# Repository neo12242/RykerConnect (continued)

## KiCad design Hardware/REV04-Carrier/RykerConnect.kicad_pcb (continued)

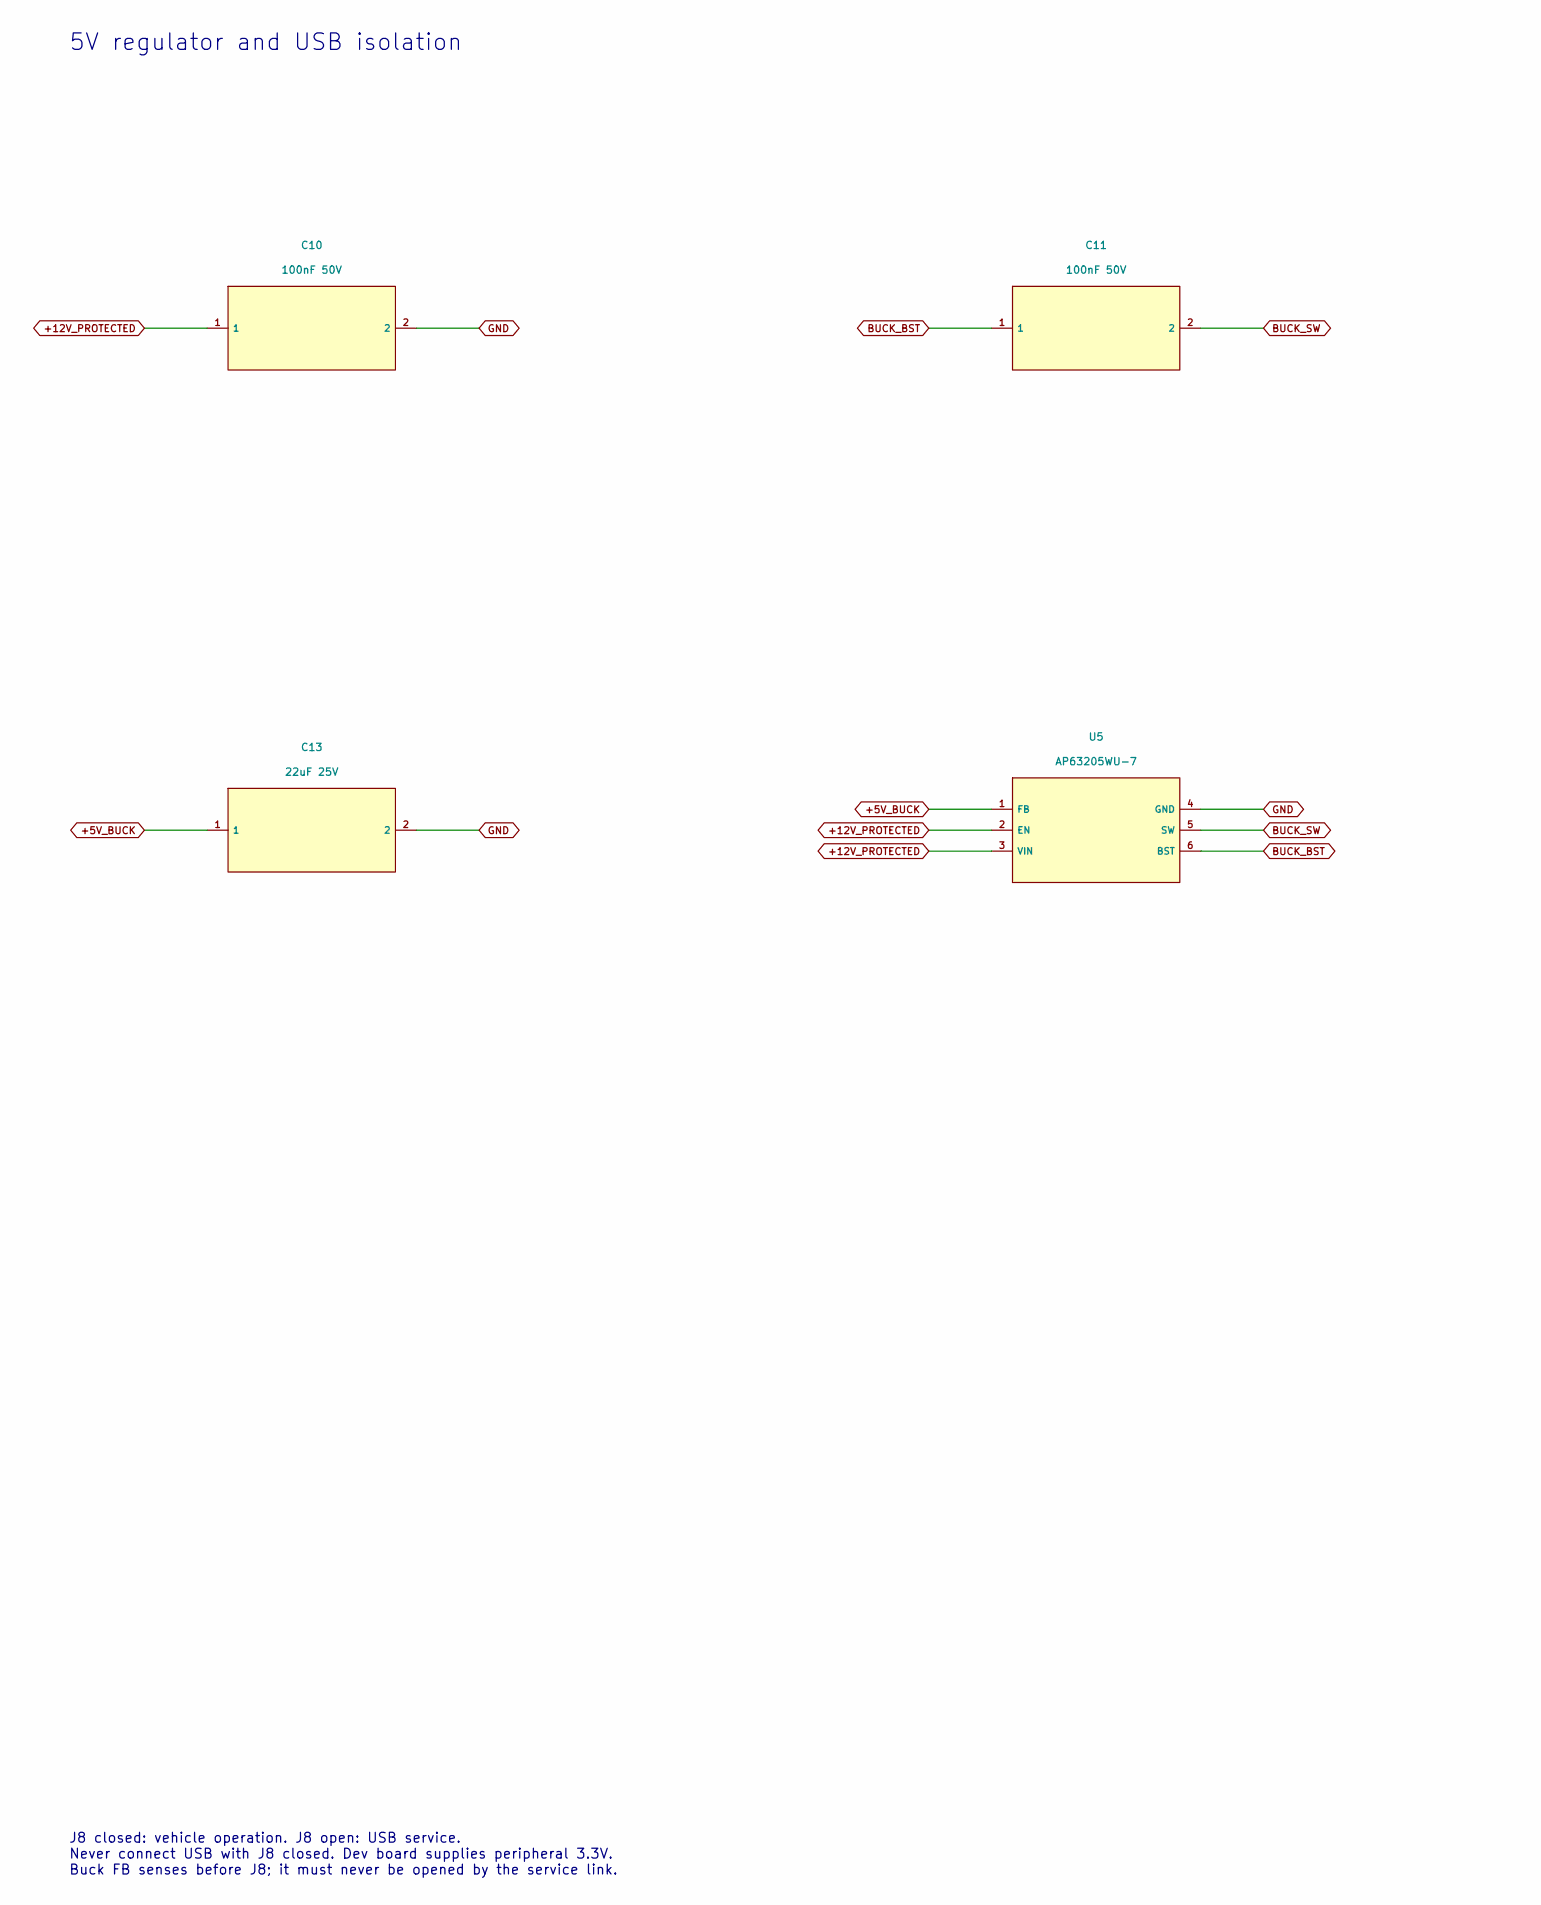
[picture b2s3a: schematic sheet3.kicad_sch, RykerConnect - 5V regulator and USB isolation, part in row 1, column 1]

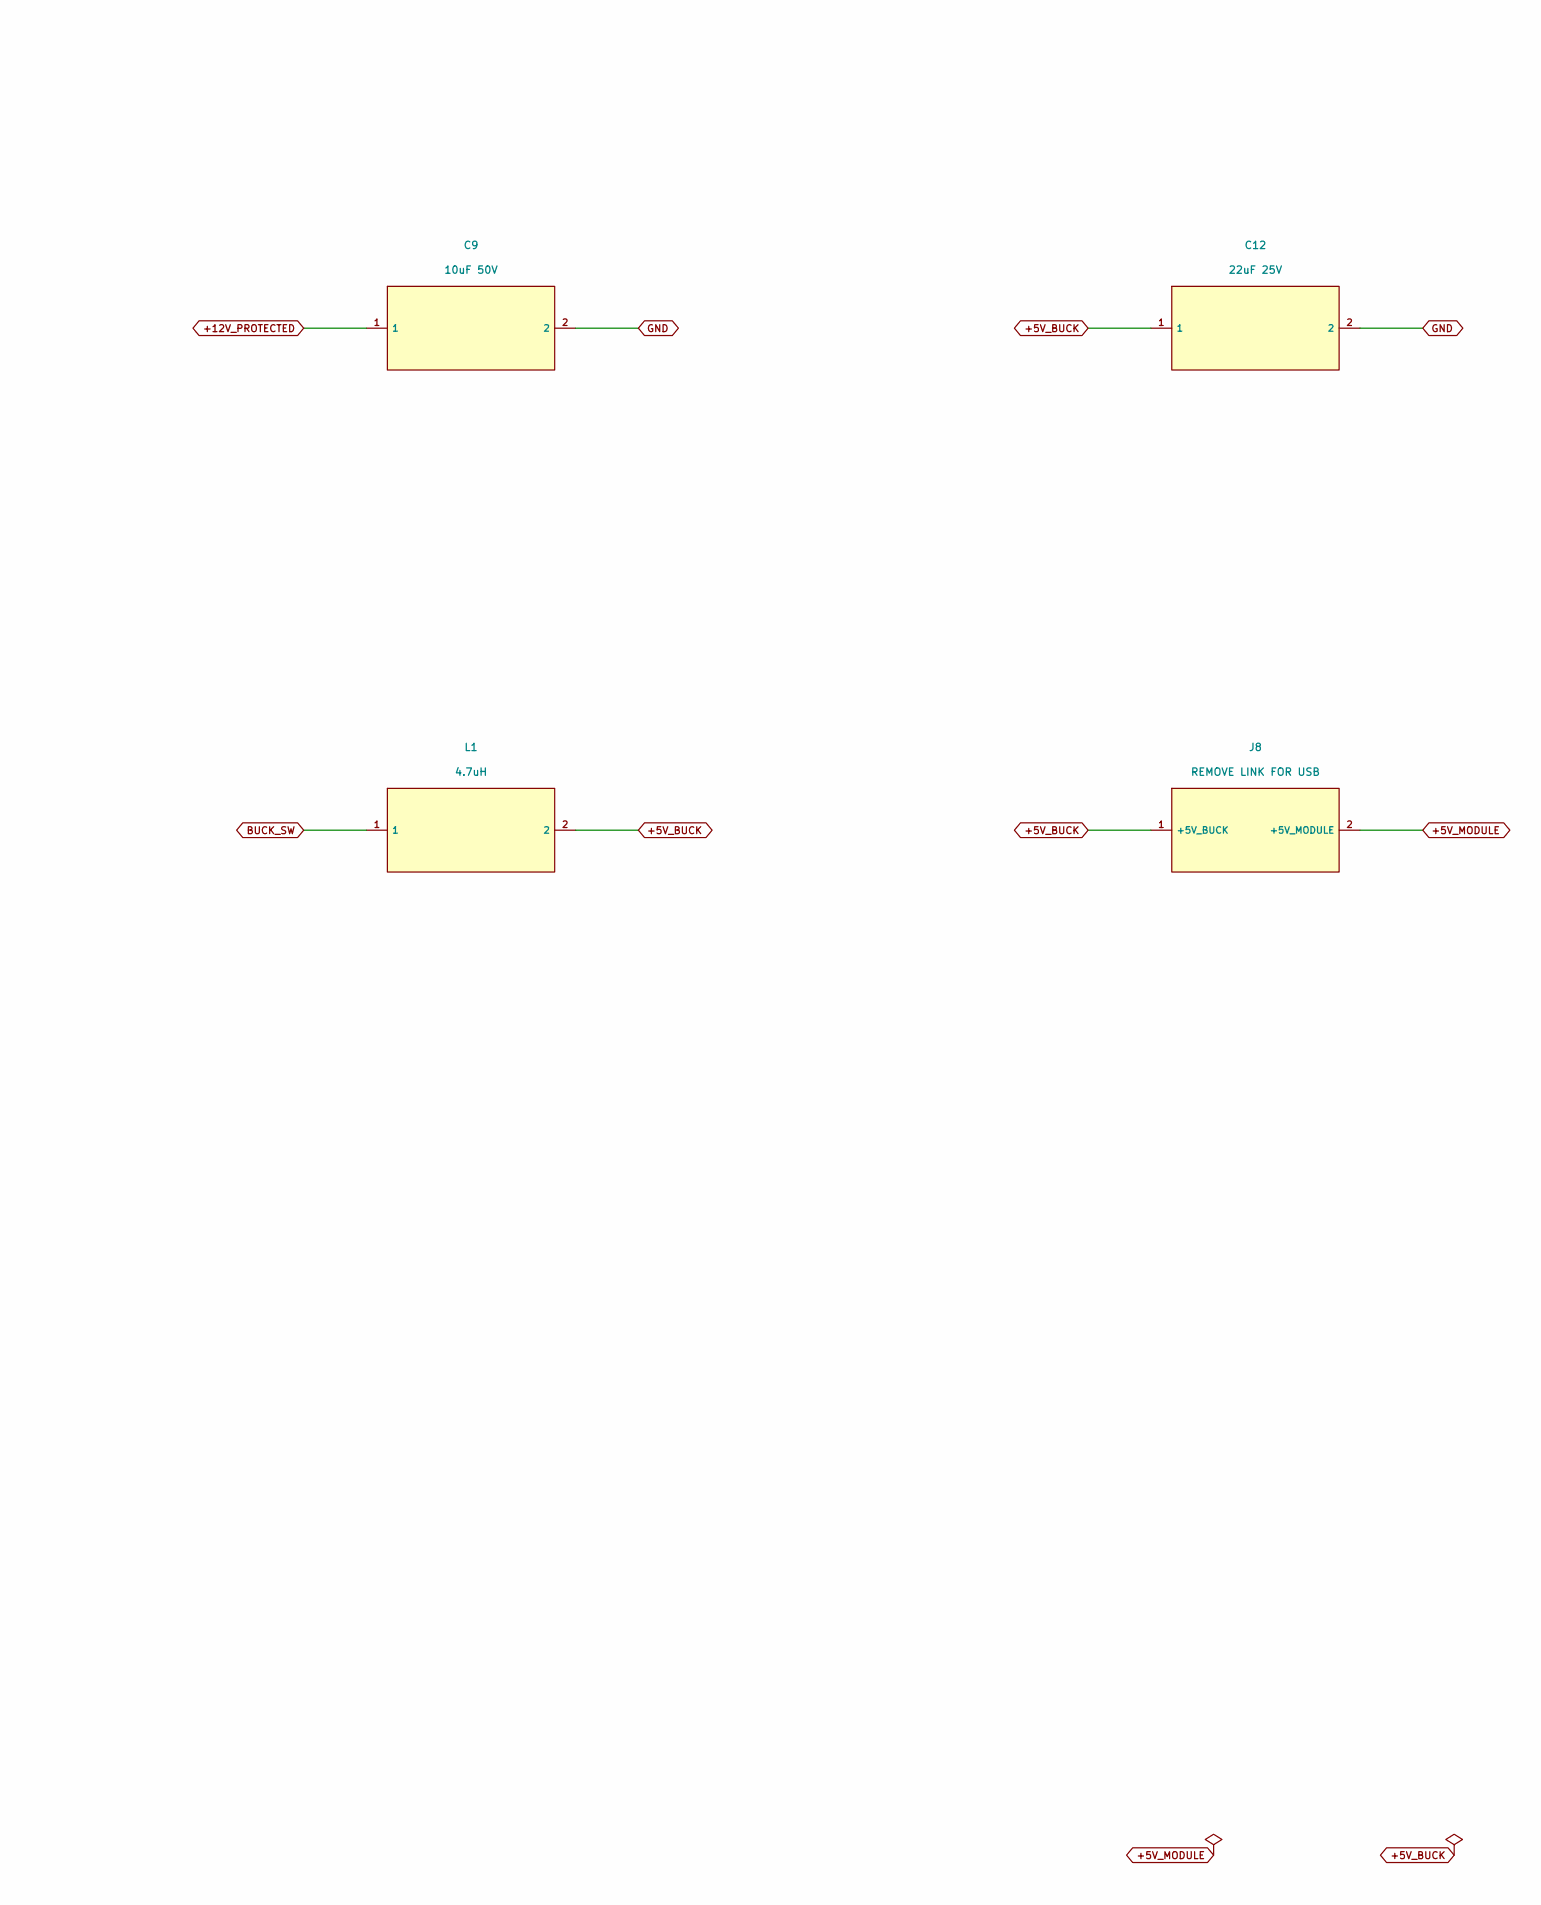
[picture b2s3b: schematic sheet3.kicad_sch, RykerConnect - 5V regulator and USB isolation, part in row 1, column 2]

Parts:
C9: 10uF 50V; C9_C_1206_3216Metric; MPN CL31A106KBHNNNE; LCSC C13585
C10: 100nF 50V; C10_C_0603_1608Metric; MPN CL10B104KB8NNNC; LCSC C1591
C11: 100nF 50V; C11_C_0603_1608Metric; MPN CL10B104KB8NNNC; LCSC C1591
C12: 22uF 25V; C12_C_0805_2012Metric; MPN CL21A226MAQNNNE; LCSC C45783
C13: 22uF 25V; C13_C_0805_2012Metric; MPN CL21A226MAQNNNE; LCSC C45783
J8: REMOVE LINK FOR USB; J8_PinHeader_1x02_P2.54mm_Vertical; MPN 5AML4-11560-102-W0; LCSC C29780898
L1: 4.7uH; L1_L1_INDPM5653X430N; MPN 744316470; LCSC C2651181
U5: AP63205WU-7; U5_TSOT-23-6; MPN AP63205WU-7; LCSC C2071056

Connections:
+5V_BUCK: C12.1, C13.1, J8.1 (+5V_BUCK), L1.2, U5.1 (FB)
+5V_MODULE: J8.2 (+5V_MODULE); also elsewhere on the board
+12V_PROTECTED: C9.1, C10.1, U5.2 (EN), U5.3 (VIN); also elsewhere on the board
BUCK_BST: C11.1, U5.6 (BST)
BUCK_SW: C11.2, L1.1, U5.5 (SW)
GND: C9.2, C10.2, C12.2, C13.2, U5.4 (GND); also elsewhere on the board

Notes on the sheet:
5V regulator and USB isolation
J8 closed: vehicle operation. J8 open: USB service. Never connect USB with J8 closed. Dev board supplies peripheral 3.3V. Buck FB senses before J8; it must never be opened by the service link.

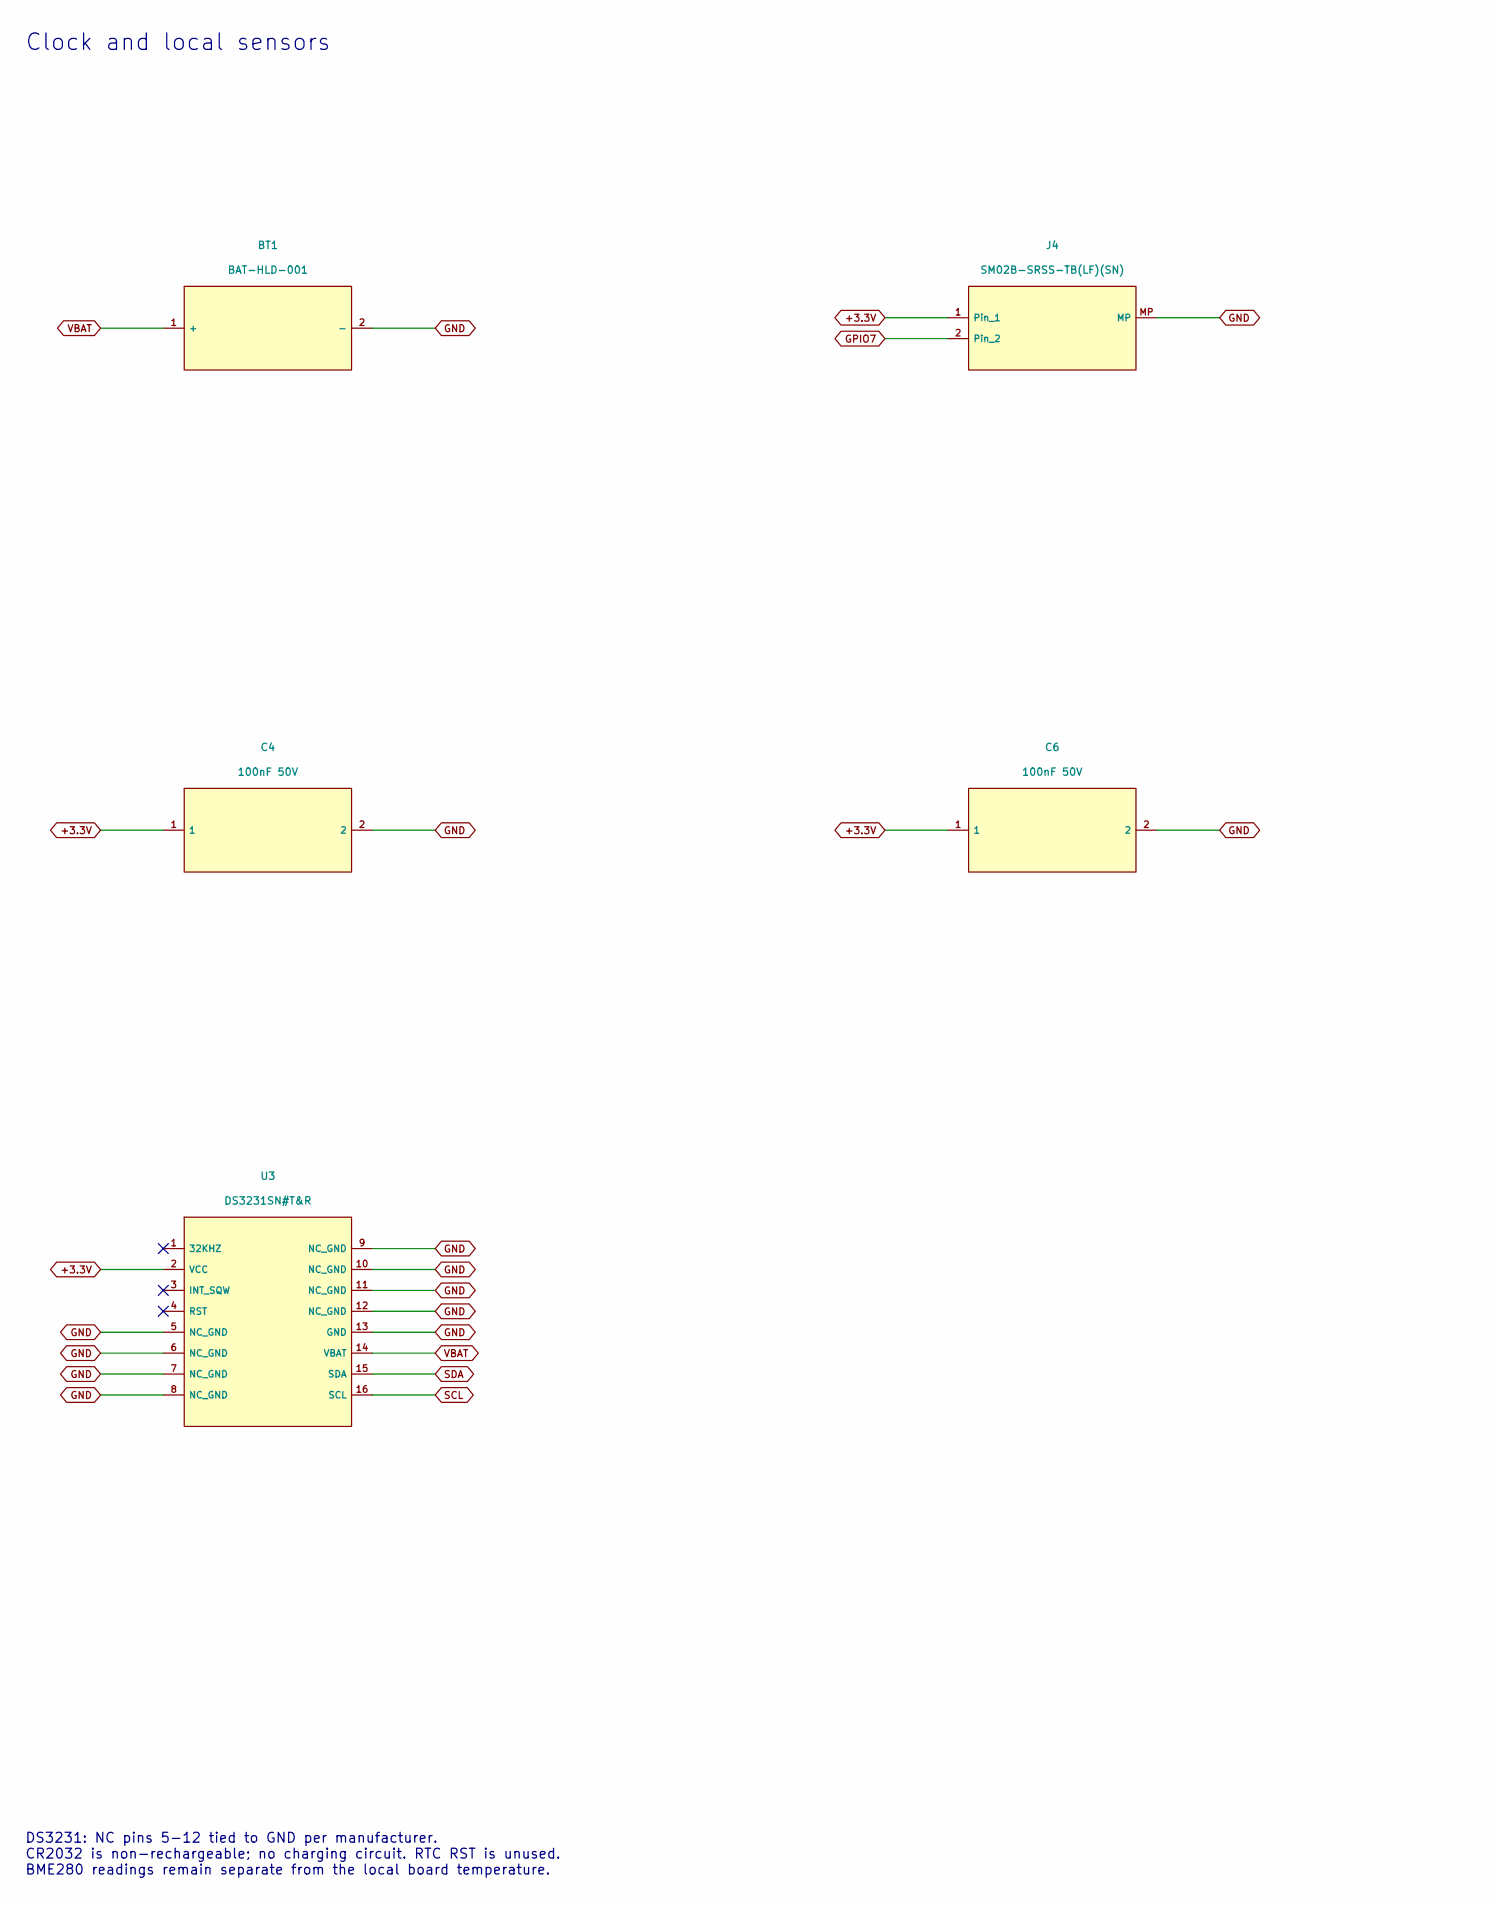
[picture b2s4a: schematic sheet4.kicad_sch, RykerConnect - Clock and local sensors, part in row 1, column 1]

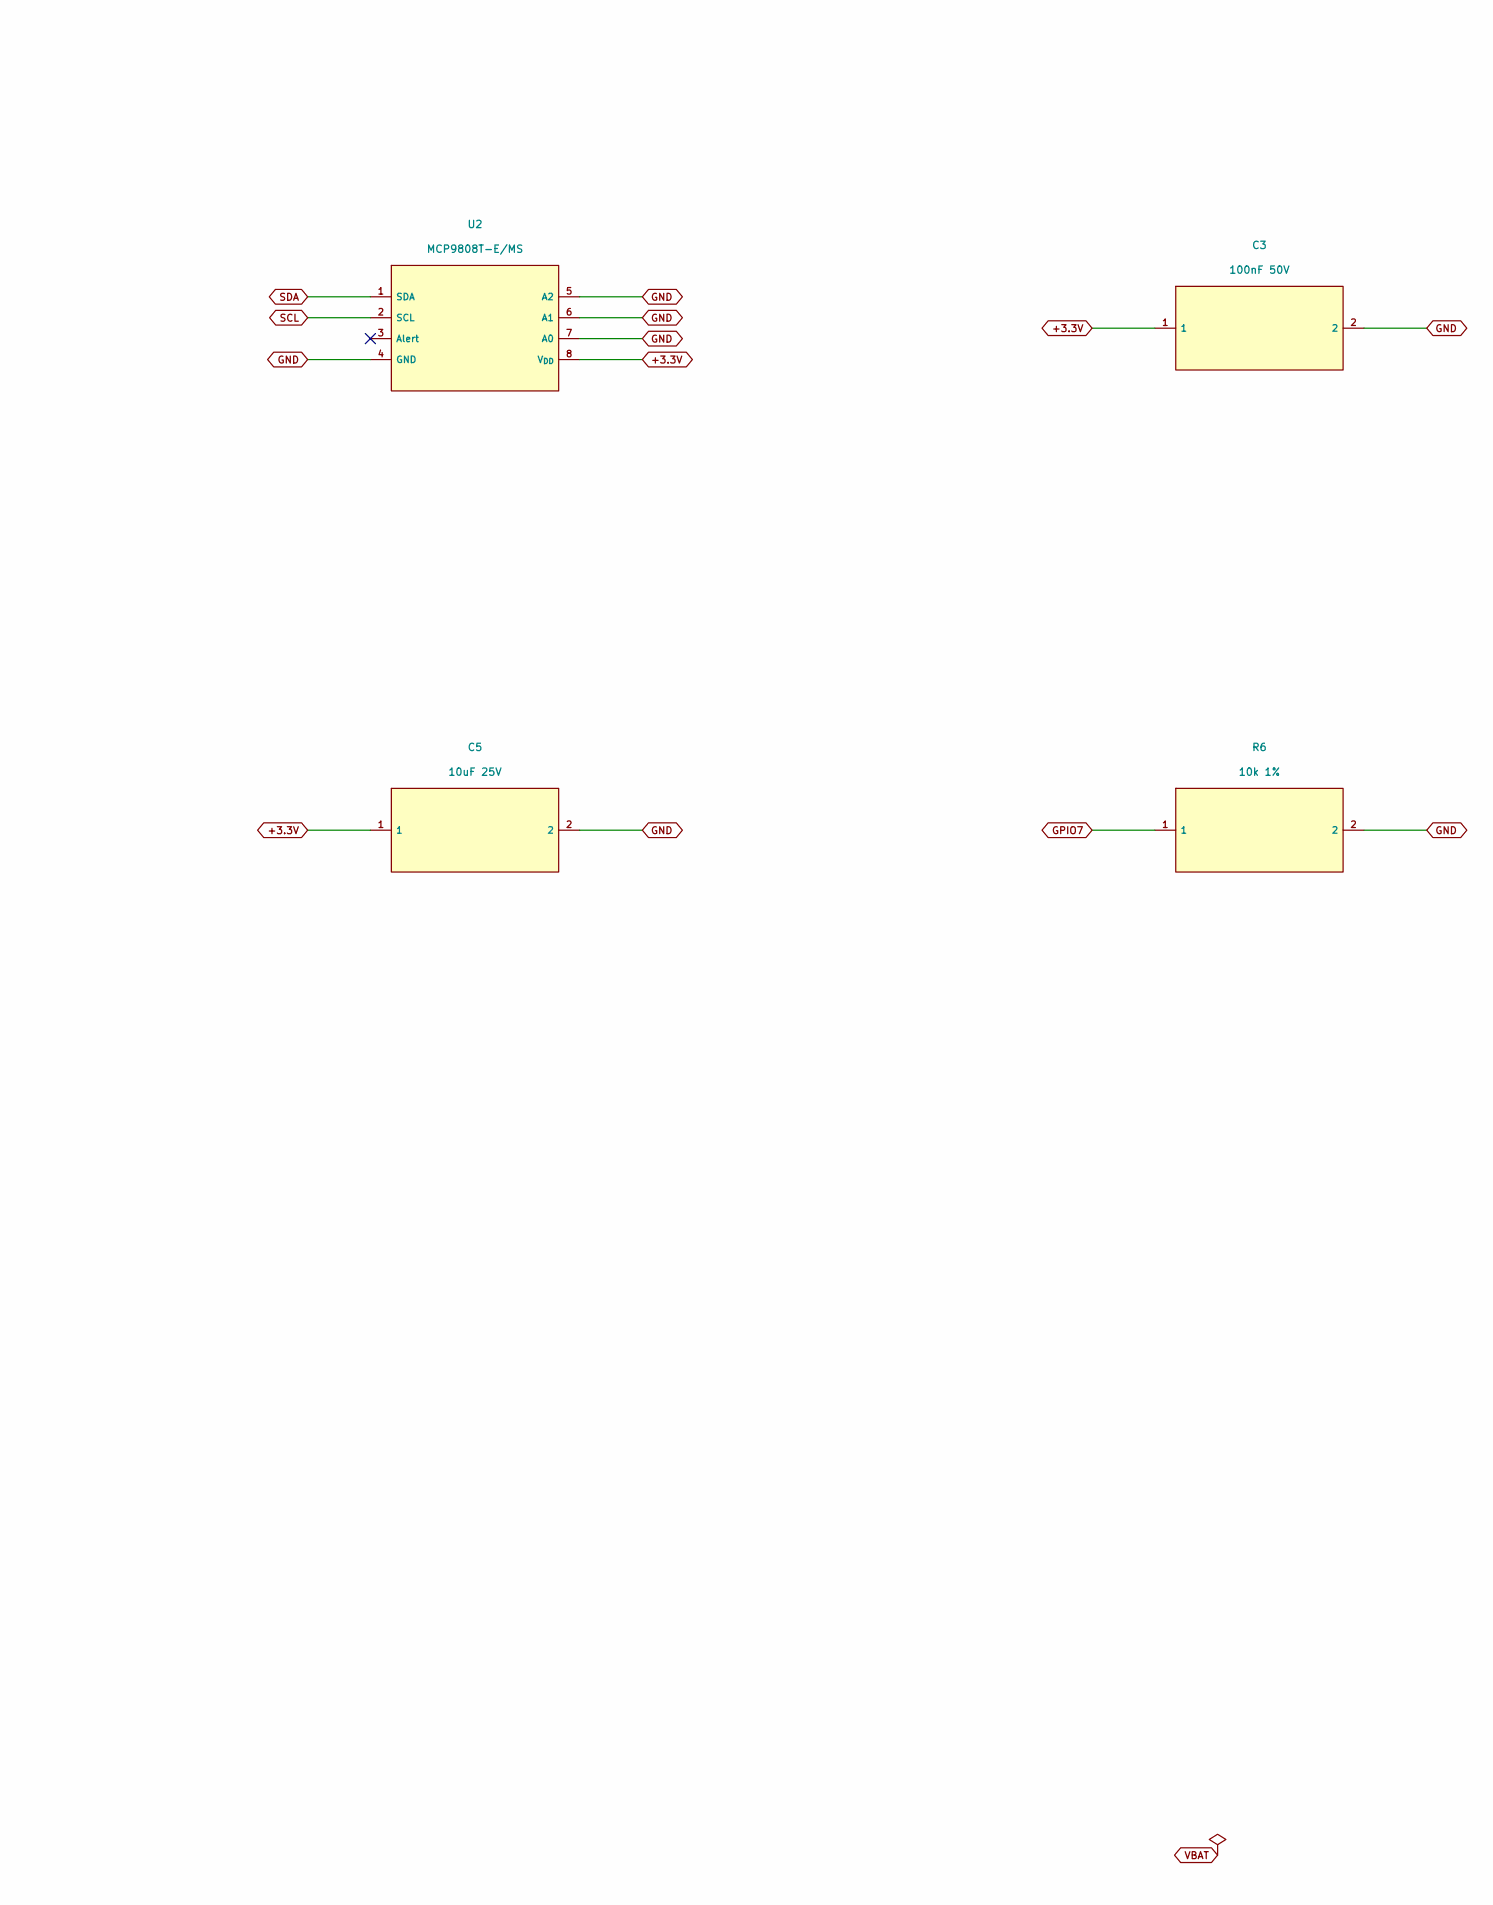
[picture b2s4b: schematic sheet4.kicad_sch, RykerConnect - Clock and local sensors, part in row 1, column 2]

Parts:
BT1: BAT-HLD-001; BT1_BT1_BATHLD001; MPN BAT-HLD-001; LCSC C7501066
C3: 100nF 50V; C3_C_0603_1608Metric; MPN CL10B104KB8NNNC; LCSC C1591
C4: 100nF 50V; C4_C_0603_1608Metric; MPN CL10B104KB8NNNC; LCSC C1591
C5: 10uF 25V; C5_C_0603_1608Metric; MPN CL10A106MA8NRNC; LCSC C96446
C6: 100nF 50V; C6_C_0603_1608Metric; MPN CL10B104KB8NNNC; LCSC C1591
J4: SM02B-SRSS-TB(LF)(SN); J4_J4_JST_SH_SM02B-SRSS-TB_1x02-1MP_P1.00mm_Horizontal; MPN SM02B-SRSS-TB(LF)(SN); LCSC C160402
R6: 10k 1%; R6_R_0603_1608Metric; MPN 0603WAF1002T5E; LCSC C25804
U2: MCP9808T-E/MS; U2_U2_MSOP-8_3x3mm_P0.65mm; MPN MCP9808T-E/MS; LCSC C129490
U3: DS3231SN#T&R; U3_SOIC-16W_7.5x10.3mm_P1.27mm; MPN DS3231SN#T&R; LCSC C9866

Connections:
+3.3V: C3.1, C4.1, C5.1, C6.1, J4.1, U2.8 (V_{DD}), U3.2 (VCC); also elsewhere on the board
GND: BT1.2 (-), C3.2, C4.2, C5.2, C6.2, J4.MP, R6.2, U2.4 (GND), U2.5 (A2), U2.6 (A1), U2.7 (A0), U3.5 (NC_GND), U3.6 (NC_GND), U3.7 (NC_GND), U3.8 (NC_GND), U3.9 (NC_GND), U3.10 (NC_GND), U3.11 (NC_GND), U3.12 (NC_GND), U3.13 (GND); also elsewhere on the board
GPIO7: J4.2, R6.1; also elsewhere on the board
SCL: U2.2 (SCL), U3.16 (SCL); also elsewhere on the board
SDA: U2.1 (SDA), U3.15 (SDA); also elsewhere on the board
VBAT: BT1.1 (+), U3.14 (VBAT)

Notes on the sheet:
Clock and local sensors
DS3231: NC pins 5-12 tied to GND per manufacturer. CR2032 is non-rechargeable; no charging circuit. RTC RST is unused. BME280 readings remain separate from the local board temperature.

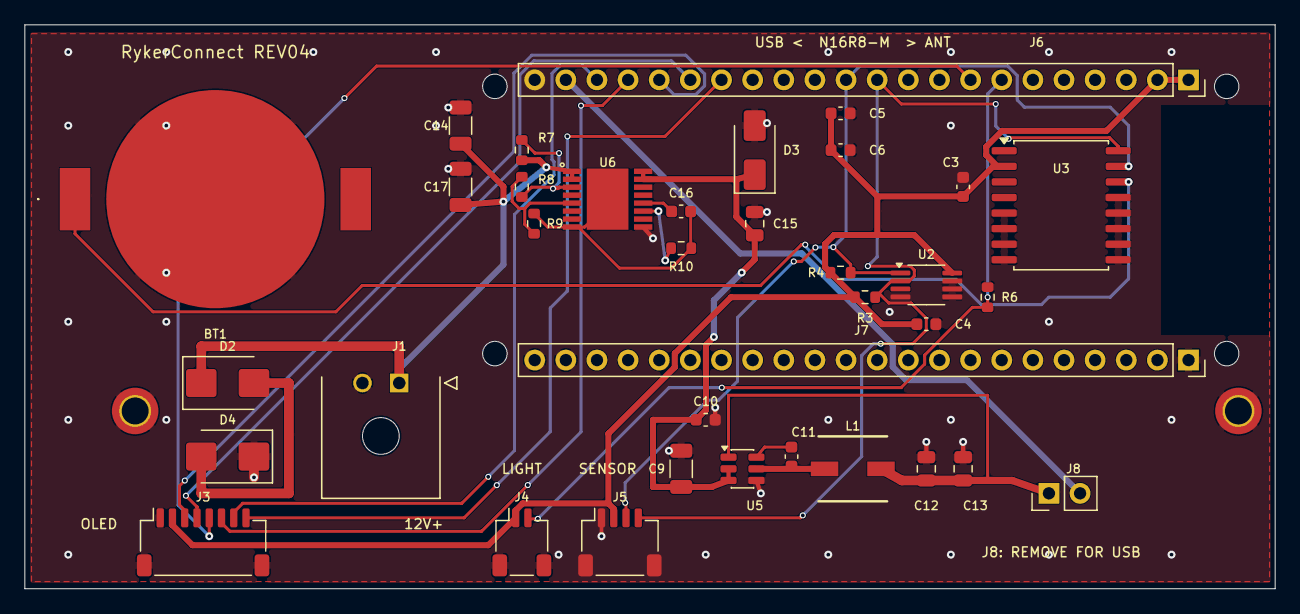
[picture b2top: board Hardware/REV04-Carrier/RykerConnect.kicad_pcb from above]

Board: 2 copper layers, 102.0 x 46.0 mm, 42 parts (1 on the bottom side), 24 nets.

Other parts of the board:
H1: MountingHole_Pad; H1_MountingHole_2.2mm_M2_ISO14580_Pad_TopBottom
H2: MountingHole_Pad; H2_MountingHole_2.2mm_M2_ISO14580_Pad_TopBottom
H3: Module retention - 2mm NPTH; H3_ModuleRetention
H4: Module retention - 2mm NPTH; H4_ModuleRetention
H5: Module retention - 2mm NPTH; H5_ModuleRetention
H6: Module retention - 2mm NPTH; H6_ModuleRetention

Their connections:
GND: H1.1 (1_1), H2.1 (1_1); also elsewhere on the board

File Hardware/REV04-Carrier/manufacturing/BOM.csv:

Comment,Designator,Footprint,LCSC Part Number,Quantity,Manufacturer,Manufacturer Part Number
BAT-HLD-001,BT1,BT1_BATHLD001,C7501066,1,TE Connectivity / Linx,BAT-HLD-001
436500200,J1,"J1_43650-02_00,01,02_",C192562,1,Molex,436500200
SM08B-SRSS-TB(LF)(SN),J3,J3_JST_SH_SM08B-SRSS-TB_1x08-1MP_P1.00mm_Horizontal,C160407,1,JST,SM08B-SRSS-TB(LF)(SN)
SM02B-SRSS-TB(LF)(SN),J4,J4_JST_SH_SM02B-SRSS-TB_1x02-1MP_P1.00mm_Horizontal,C160402,1,JST,SM02B-SRSS-TB(LF)(SN)
SM04B-SRSS-TB(LF)(SN),J5,J5_JST_SH_SM04B-SRSS-TB_1x04-1MP_P1.00mm_Horizontal,C160404,1,JST,SM04B-SRSS-TB(LF)(SN)
MCP9808T-E/MS,U2,U2_MSOP-8_3x3mm_P0.65mm,C129490,1,Microchip,MCP9808T-E/MS
TPS26600PWPR,U6,U6_Protection_HTSSOP16_PWP0016A,C544399,1,Texas Instruments,TPS26600PWPR
SMBJ33A,D2,D_SMB,C224019,1,Littelfuse,SMBJ33A
B140-13-F,D3,D_SMA,C15759,1,Diodes Incorporated,B140-13-F
1uF 100V,"C14,C17",C_1206_3216Metric,C13832,2,Samsung Electro-Mechanics,CL31B105KCHNNNE
1uF 50V,C15,C_0805_2012Metric,C28323,1,Samsung Electro-Mechanics,CL21B105KBFNNNE
10nF 50V,C16,C_0603_1608Metric,C1589,1,Samsung Electro-Mechanics,CL10B103KB8NNNC
120k 1%,R7,R_0603_1608Metric,C114607,1,Yageo,RC0603FR-07120KL
20k 1%,R8,R_0603_1608Metric,C105575,1,Yageo,RC0603FR-0720KL
10k,"R9,R6",R_0603_1608Metric,C25804,2,UNI-ROYAL,0603WAF1002T5E
12k 1%,R10,R_0603_1608Metric,C114659,1,Yageo,RC0603FR-0712KL
SMBJ18A,D4,D_SMB,C151256,1,Littelfuse,SMBJ18A
100nF 50V,"C3,C4,C6,C10,C11",C_0603_1608Metric,C1591,5,Samsung Electro-Mechanics,CL10B104KB8NNNC
10uF 25V,C5,C_0603_1608Metric,C96446,1,Samsung Electro-Mechanics,CL10A106MA8NRNC
10uF 50V,C9,C_1206_3216Metric,C13585,1,Samsung Electro-Mechanics,CL31A106KBHNNNE
22uF 25V,"C12,C13",C_0805_2012Metric,C45783,2,Samsung Electro-Mechanics,CL21A226MAQNNNE
4.7k 1%,"R3,R4",R_0603_1608Metric,C23162,2,UNI-ROYAL,0603WAF4701T5E
DS3231SN#T&R,U3,SOIC-16W_7.5x10.3mm_P1.27mm,C9866,1,Analog Devices,DS3231SN#T&R
AP63205WU-7,U5,TSOT-23-6,C2071056,1,Diodes Incorporated,AP63205WU-7
4.7uH,L1,L1_INDPM5653X430N,C2651181,1,Wurth Elektronik,744316470
ESP32 socket P1,"J6,J7",PinSocket_1x22_P2.54mm_Vertical,C7500786,2,XUNPU,FH2.54-09-22PZD
REMOVE LINK FOR USB,J8,PinHeader_1x02_P2.54mm_Vertical,C29780898,1,SAMZO,5AML4-11560-102-W0
